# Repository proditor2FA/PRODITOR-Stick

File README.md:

# PRODITOR Solution

https://www.proditor.de

Advanced eight-digit two-factor HOTP solution. Designed to secure remote desktop access.

USB key based on the ATSAM-D11C14 microcontroller. 

This project was build using [Microchip Studio](https://www.microchip.com/en-us/tools-resources/develop/microchip-studio) and [KiCAD](https://www.kicad.org/)

(https://www.proditor.de)

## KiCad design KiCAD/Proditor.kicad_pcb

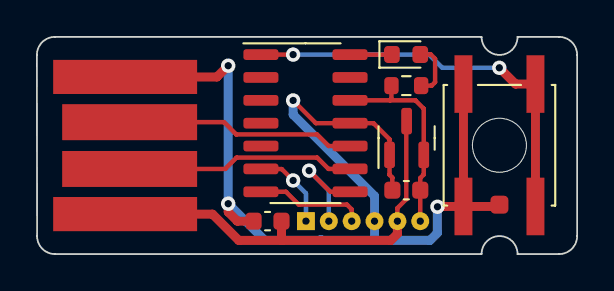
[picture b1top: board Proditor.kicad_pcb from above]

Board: 2 copper layers, 30.0 x 12.1 mm, 10 parts (0 on the bottom side), 11 nets.

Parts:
C1, C2: 1uf; C_0603_1608Metric
D1: LED; LED_0603_1608Metric_Mod
H1: MountingHole; MountingHole_3mm
J1: USB_A_PCB; USB-PCB
J2: SWD; PinHeader_1x06_P1.27mm_Vertical_Via0.4mm
R1: 100; R_0603_1608Metric
SW1: SW_Push; SW_SPST_EVQQ2_GND
U1: ATSAMD11C14A-SS; SOIC-14_3.9x8.7mm_P1.27mm
U2: MCP1700x-3V3; SOT-23

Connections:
unnamed: D1.2 (A), R1.1
unnamed: D1.1 (K), U1.14 (PA04)
unnamed: J1.3 (D+), U1.10 (PA25)
unnamed: J1.2 (D-), U1.9 (PA24)
unnamed: C1.2, C2.2, J1.4 (GND), J2.4, SW1.1, U1.11 (GND), U2.1 (GND)
unnamed: C1.1, J1.1 (VBUS), J2.5, U2.3 (VI)
unnamed: J2.1, U1.6 (PA28/~RST)
unnamed: J2.2, U1.8 (PA31/SWDIO)
unnamed: J2.3, U1.7 (PA30/SWCLK)
unnamed: C2.1, J2.6, R1.2, U1.12 (VDD), U2.2 (VO)
unnamed: SW1.2, U1.1 (PA05)

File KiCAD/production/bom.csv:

Designator,Footprint,Quantity,Value,LCSC Part #
"C1, C2",0603,2,1uf,
D1,0603,1,LED,
H1,MountingHole_3mm,1,MountingHole,
J1,USB-PCB,1,USB_A_PCB,
J2,PinHeader_1x06_P1.27mm_Vertical_Via0.4mm,1,SWD,
R1,0603,1,100,
SW1,SW_SPST_EVQQ2,1,SW_Push,
U1,SOIC-14_3.9x8.7mm_P1.27mm,1,ATSAMD11C14A-SS,
U2,SOT-23,1,MCP1700x-3V3,

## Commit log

2023-09-08 initial push
2023-10-06 GPL fix
2023-11-21 USB NumLock fix
2024-04-27 add pictures
